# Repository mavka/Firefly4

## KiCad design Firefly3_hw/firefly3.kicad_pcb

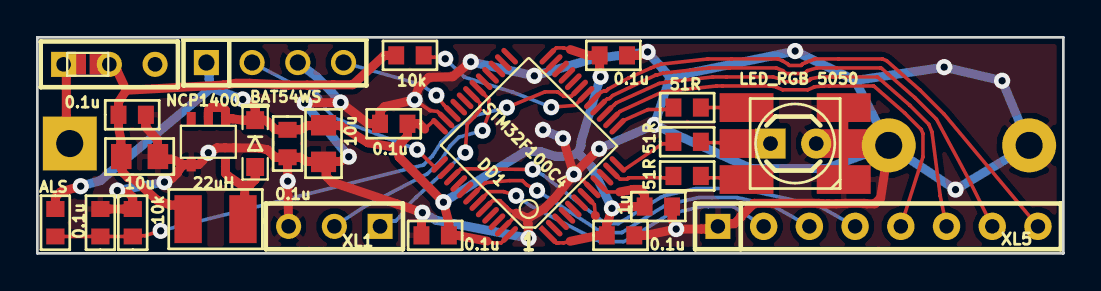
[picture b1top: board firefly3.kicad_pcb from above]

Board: 2 copper layers, 57.0 x 12.0 mm, 31 parts (0 on the bottom side), 25 nets.

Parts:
C1, C2, C3, C4, C5, C6, C8: 0.1u; CAP_0603
C7, C9: 10u; CAP_0805
C10: 1u; CAP_0603
D1: BAT54WS; DIODE_SOD323
D2: LED; LED-3MM
DA1: NCP1400; SOT23-5
DD1: STM32F100C4; LQFP48
F1: FUSE0R; SMD0603_FUSE
L1: 22uH; IND_1210
Q1: ALS; RES_0603
Q2: LED_RGB 5050; LED_HH5050_RGB
R1, R3, R4: 51R; RES_0603
R2, R5: 10k; RES_0603
SW1: SWITCH; SIL-3
TP1: TESTPOINT; TESTPOINT_0_5MM
XL1: CONN_3; SIL-3
XL2: ST_SWD; SIL-4
XL3: CONN_1; SIL1_SQUARE_1MM5
XL4, XL6: CONN_1; SIL1_ROUND_1MM5
XL5: CONN_8; SIL-8

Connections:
+3.3V: C2.1, C3.1, C4.1, C5.1, C8.1, C9.1, C10.1, D1.C, DA1.1, DA1.2, DD1.1, DD1.9, DD1.24, DD1.36, DD1.48, Q1.1, XL2.1
+BATT: C6.1, C7.1, F1.2, L1.2, R2.1, SW1.2
/2: DD1.43, XL5.2
/3: DD1.42, XL5.3
/4: DD1.39, XL5.4
/5: DD1.14, XL5.5
/6: DD1.15, XL5.6
/7: DD1.16, XL5.7
/8: DD1.17, XL5.8
/BAT_IN: F1.1, SW1.1, XL3.1
/Lout: D1.A, DA1.5, L1.1
/RX: DD1.31, XL1.1
/SB_SWCLK: DD1.37, XL2.2
/SB_SWDAT: DD1.34, XL2.4
/TX: DD1.30, XL1.2
GND: C1.2, C2.2, C3.2, C4.2, C5.2, C6.2, C7.2, C8.2, C9.2, C10.2, D2.C, DA1.4, DD1.8, DD1.23, DD1.35, DD1.44, DD1.47, Q2.BC, Q2.GC, Q2.RC, R5.2, XL1.3, XL2.3, XL4.1, XL5.1, XL6.1
unnamed: DD1.18, R2.2
unnamed: DD1.7, TP1.1
unnamed: C1.1, DD1.19, Q1.2, R5.1
unnamed: Q2.BA, R4.2
unnamed: DD1.13, R3.1
unnamed: DD1.12, R1.1
unnamed: DD1.11, R4.1
unnamed: D2.A, Q2.RA, R1.2
unnamed: Q2.GA, R3.2

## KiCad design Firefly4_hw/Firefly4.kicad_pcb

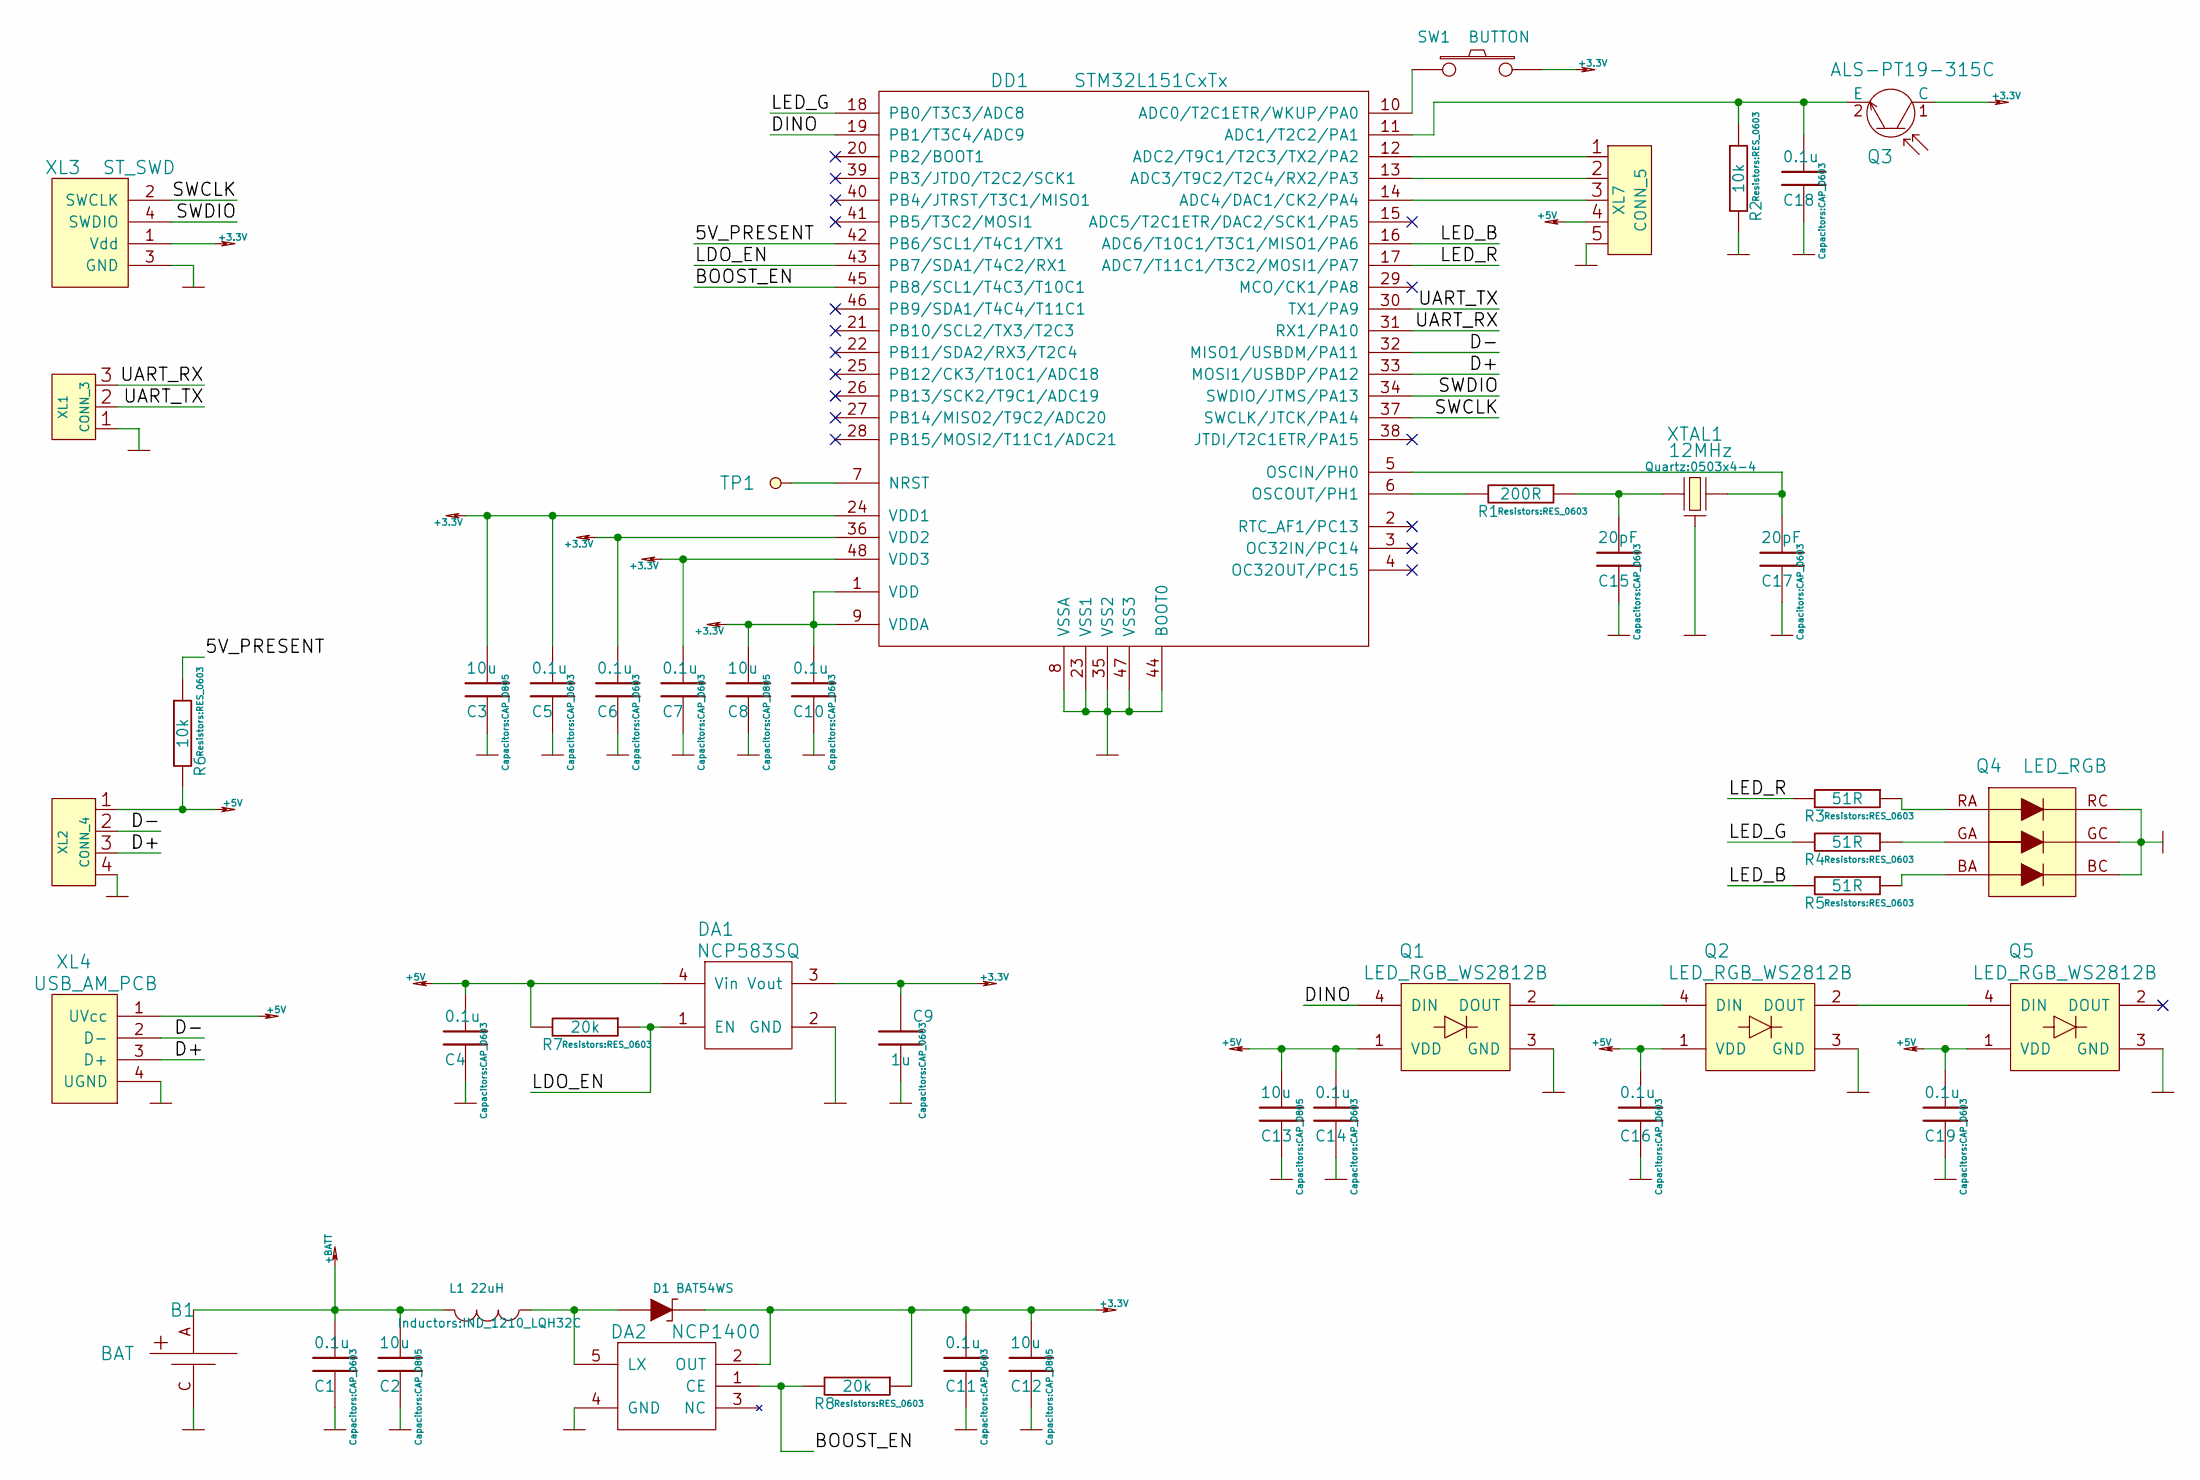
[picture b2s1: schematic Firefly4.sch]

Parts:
B1: BAT; BATTERY_AA_X1
C1, C4, C5, C6, C7, C10, C11, C14, C16, C18, C19: 0.1u; CAP_0603
C2, C3, C8, C12, C13: 10u; CAP_0805
C9: 1u; CAP_0603
C15, C17: 20pF; CAP_0603
D1: BAT54WS; SOD323
DA1: NCP583SQ; SC82AB
DA2: NCP1400; SOT23-5
DD1: STM32L151CxTx; LQFP48
L1: 22uH; IND_1210_LQH32C
Q1, Q2, Q5: LED_RGB_WS2812B; LED_WS2812B
Q3: ALS-PT19-315C; RES_0603
Q4: LED_RGB; LED_5050
R1: 200R; RES_0603
R2, R6: 10k; RES_0603
R3, R4, R5: 51R; RES_0603
R7, R8: 20k; RES_0603
SW1: BUTTON; BTN_4x4_SMD
TP1: TESTPOINT; TESTPOINT_1MM
XL1: CONN_3; PLS-3
XL2: CONN_4; PLS-4
XL3: ST_SWD; PLS-4
XL4: USB_AM_PCB
XL7: CONN_5; PLS-5
XTAL1: 12MHz; 0503x4-4

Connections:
+3.3V: C3.1, C5.1, C6.1, C7.1, C8.1, C9.1, C10.1, C11.1, C12.1, D1.C, DA1.3 (Vout), DA2.2 (OUT), DD1.1 (VDD), DD1.9 (VDDA), DD1.24 (VDD1), DD1.36 (VDD2), DD1.48 (VDD3), Q3.1 (C), R8.1, SW1.2, XL3.1 (Vdd)
+5V: C4.1, C13.1, C14.1, C16.1, C19.1, DA1.4 (Vin), Q1.1 (VDD), Q2.1 (VDD), Q5.1 (VDD), R6.2, R7.2, XL2.1, XL4.1 (UVcc), XL7.4
+BATT: B1.A, C1.1, C2.1, L1.2
/5V_PRESENT: DD1.42 (PB6/SCL1/T4C1/TX1), R6.1
/BOOST_EN: DA2.1 (CE), DD1.45 (PB8/SCL1/T4C3/T10C1), R8.2
/D+: DD1.33 (MOSI1/USBDP/PA12), XL2.3, XL4.3 (D+)
/D-: DD1.32 (MISO1/USBDM/PA11), XL2.2 (PM), XL4.2 (D-)
/DINO: DD1.19 (PB1/T3C4/ADC9), Q1.4 (DIN)
/LDO_EN: DA1.1 (EN), DD1.43 (PB7/SDA1/T4C2/RX1), R7.1
/LED_B: DD1.16 (ADC6/T10C1/T3C1/MISO1/PA6), R5.2
/LED_G: DD1.18 (PB0/T3C3/ADC8), R4.2
/LED_R: DD1.17 (ADC7/T11C1/T3C2/MOSI1/PA7), R3.2
/SWCLK: DD1.37 (SWCLK/JTCK/PA14), XL3.2 (SWCLK)
/SWDIO: DD1.34 (SWDIO/JTMS/PA13), XL3.4 (SWDIO)
/UART_RX: DD1.31 (RX1/PA10), XL1.3
/UART_TX: DD1.30 (TX1/PA9), XL1.2 (PM)
GND: B1.C, C1.2, C2.2, C3.2, C4.2, C5.2, C6.2, C7.2, C8.2, C9.2, C10.2, C11.2, C12.2, C13.2, C14.2, C15.2, C16.2, C17.2, C18.2, C19.2, DA1.2 (GND), DA2.4 (GND), DD1.8 (VSSA), DD1.23 (VSS1), DD1.35 (VSS2), DD1.44 (BOOT0), DD1.47 (VSS3), Q1.3 (GND), Q2.3 (GND), Q4.BC (B), Q4.GC (G), Q4.RC, Q5.3 (GND), R2.2, XL1.1, XL2.4, XL3.3 (GND), XL4.4 (UGND), XL7.5, XTAL1.H
unnamed: C15.1, R1.1, XTAL1.1
unnamed: C17.1, DD1.5 (OSCIN/PH0), XTAL1.2
unnamed: C18.1, DD1.11 (ADC1/T2C2/PA1), Q3.2 (E), R2.1
unnamed: D1.A, DA2.5 (LX), L1.1
unnamed: DD1.6 (OSCOUT/PH1), R1.2
unnamed: DD1.7 (NRST), TP1.1
unnamed: DD1.10 (ADC0/T2C1ETR/WKUP/PA0), SW1.1
unnamed: DD1.12 (ADC2/T9C1/T2C3/TX2/PA2), XL7.1
unnamed: DD1.13 (ADC3/T9C2/T2C4/RX2/PA3), XL7.2
unnamed: DD1.14 (ADC4/DAC1/CK2/PA4), XL7.3
unnamed: Q1.2 (DOUT), Q2.4 (DIN)
unnamed: Q2.2 (DOUT), Q5.4 (DIN)
unnamed: Q4.BA, R5.1
unnamed: Q4.GA, R4.1
unnamed: Q4.RA, R3.1

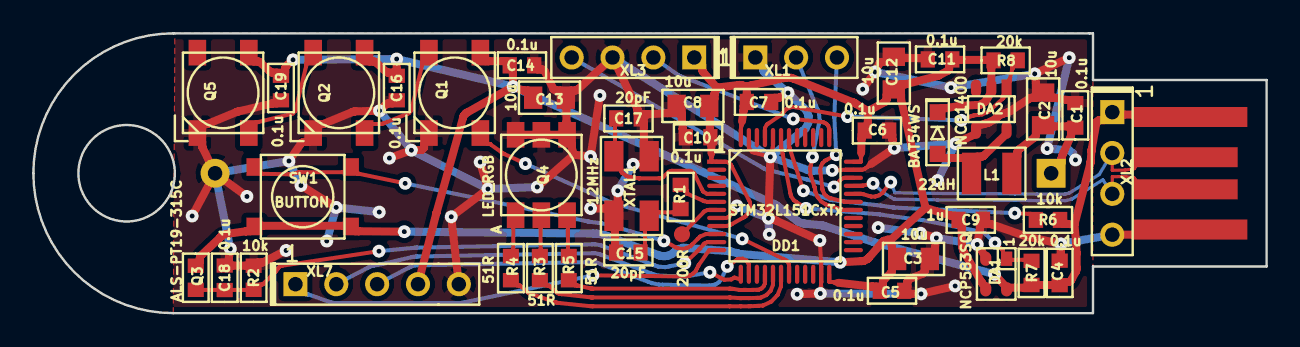
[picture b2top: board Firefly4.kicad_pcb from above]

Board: 2 copper layers, 76.7 x 17.4 mm, 46 parts (1 on the bottom side), 32 nets.

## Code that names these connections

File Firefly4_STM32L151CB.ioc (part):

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Mcu.Name=STM32L151C(6-8-B)Tx
Mcu.Package=LQFP48
Mcu.UserName=STM32L151CBTx
PA1.Mode=IN1
PA1.Signal=ADC_IN1
PA10.Mode=Asynchronous
PA10.Signal=USART1_RX
PA11.Mode=Device
PA11.Signal=USB_DM
PA12.Mode=Device
PA12.Signal=USB_DP
PA13.Mode=Serial-Wire
PA13.Signal=SYS_JTMS-SWDIO
PA14.Mode=Serial-Wire
PA14.Signal=SYS_JTCK-SWCLK
PA6.GPIOParameters=GPIO_Label
PA6.GPIO_Label=LED1_R
PA6.Signal=S_TIM3_CH1
PA7.GPIOParameters=GPIO_Label
PA7.GPIO_Label=LED1_G
PA7.Signal=S_TIM3_CH2
PA9.Mode=Asynchronous
PA9.Signal=USART1_TX
PB0.GPIOParameters=GPIO_Label
PB0.GPIO_Label=LED1_B
PB0.Signal=S_TIM3_CH3
PB1.GPIOParameters=GPIO_Label
PB1.GPIO_Label=DINO
PB1.Signal=S_TIM3_CH4
PH0-OSC_IN.Mode=HSE-External-Oscillator
PH0-OSC_IN.Signal=RCC_OSC_IN
PH1-OSC_OUT.Mode=HSE-External-Oscillator
PH1-OSC_OUT.Signal=RCC_OSC_OUT
RCC.HSE_VALUE=24000000
RCC.SYSCLKFreq_VALUE=2097000

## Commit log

2015-12-07 + cube for F072C8 and L151CB
2015-12-11 sch update, need check
2015-12-15 Sch seems completed
2015-12-15 sch update
2015-12-15 + LDO & Booster control
2015-12-15 + CvPcb
2015-12-16 + TopoR
2015-12-17 pcb done + gerber
2015-12-19 just ignore it
2015-12-25 + FW started
2015-12-26 + Compiled, not tested
2015-12-26 + Compiled, UART works correctly
2015-12-26 + message added to sysHalt + 5v sns + HSI48 clocking
2015-12-27 + USB connected successfully. USB CDC RX still not implemented.
2015-12-28 + USB Shell works
2015-12-28 + LedWS seems working + Shell Get Array
2015-12-28 + TerminalMacro + Update sys timer on UpdateFreqs + OnAHBFreqChange in WS LED works
2015-12-28 + USB control
2015-12-29 Proceeding with keybrd
2015-12-29 Something hangs up.
2015-12-29 CDC ok
2015-12-29 + Keybrd works, but HID_REQ_SetReport hangs
2015-12-29 Proceeding
2016-01-11 ADC ok, but USB fails
2016-01-21 * Cleanup
2016-01-21 * WS2812 constants * WS2812 data flow: data and reset replaced each other
2016-02-25 Proceeding with new algorythm
2016-02-25 + Firefly3 with new firmware
2016-02-26 * Switch to next version of OS - Clocking
2016-02-26 * USB does not work
2016-02-26 Cleanup, RC
2016-02-27 * Cmd+Space + Modifiers
2016-03-01 Back to 'a' letter
2016-04-19 + Firefly3: random color change
2016-05-24 Release
